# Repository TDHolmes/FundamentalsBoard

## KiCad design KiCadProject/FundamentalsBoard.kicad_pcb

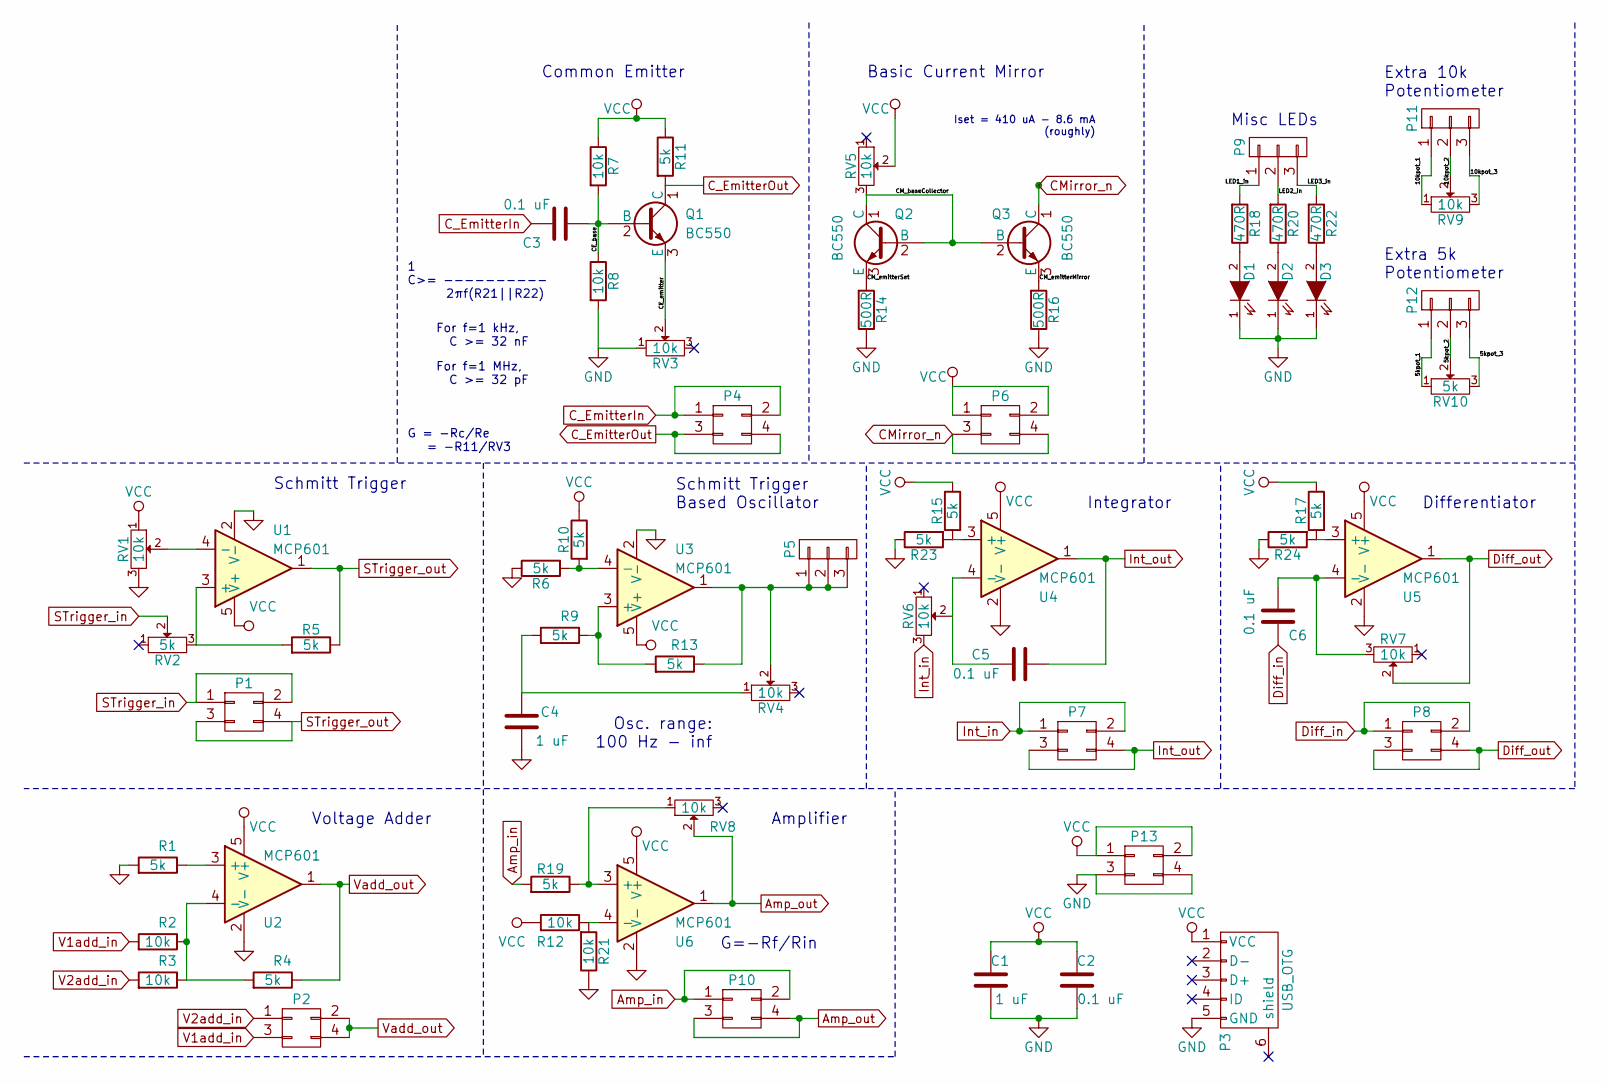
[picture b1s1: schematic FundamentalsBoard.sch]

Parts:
C1, C4: 1 uF; C_0603
C2, C3, C5, C6: 0.1 uF; C_0603
D1, D2, D3: LED; LED_0603
P1, P2, P4, P6, P7, P8, P10, P13: CONN_02X02; Pin_Header_Straight_2x02
P3: USB_OTG; 2013499-1
P5, P9, P11, P12: CONN_01X03; Pin_Header_Straight_1x03
Q1, Q2, Q3: BC550; SOT-23
R1, R4, R5, R6, R9, R10, R11, R13, R15, R17, R19, R23, R24: 5k; R_0603
R2, R3, R7, R8, R12, R21: 10k; R_0603
R14, R16: 500R; R_0603
R18, R20, R22: 470R; R_0603
RV1, RV3, RV4, RV5, RV6, RV7, RV8, RV9: 10k; ST-4
RV2, RV10: 5k; ST-4
U1, U2, U3, U4, U5, U6: MCP601; SOT-23-5

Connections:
/5kpot_1: P12.1, RV10.1
/5kpot_2: P12.2, RV10.2
/5kpot_3: P12.3, RV10.3
/10kpot_1: P11.1, RV9.1
/10kpot_2: P11.2, RV9.2
/10kpot_3: P11.3, RV9.3
/CE_base: C3.1, Q1.2 (B), R7.2, R8.1
/CE_emitter: Q1.3 (E), RV3.2
/CM_baseCollector: Q2.1 (C), Q2.2 (B), Q3.2 (B), RV5.3
/CM_emitterMirror: Q3.3 (E), R16.2
/CM_emitterSet: Q2.3 (E), R14.2
/LED1_in: P9.1, R18.2
/LED2_in: P9.2, R20.2
/LED3_in: P9.3, R22.2
Amp_in: P10.1, P10.2, R19.2
Amp_out: P10.3, P10.4, RV8.2, U6.1
CMirror_n: P6.3, P6.4, Q3.1 (C)
C_EmitterIn: C3.2, P4.1, P4.2
C_EmitterOut: P4.3, P4.4, Q1.1 (C), R11.2
Diff_in: C6.1, P8.1, P8.2
Diff_out: P8.3, P8.4, RV7.2, U5.1
GND: C1.1, C2.1, C4.1, D1.1 (K), D2.1 (K), D3.1 (K), P3.5 (GND), P13.3, P13.4, R1.2, R6.1, R8.2, R14.1, R16.1, R21.1, R23.1, R24.1, RV1.3, RV3.1, U1.2 (V-), U2.2 (V-), U3.2 (V-), U4.2 (V-), U5.2 (V-), U6.2 (V-)
Int_in: P7.1, P7.2, RV6.3
Int_out: C5.2, P7.3, P7.4, U4.1
unnamed: C4.2, R9.2, RV4.1
unnamed: C5.1, U4.4 (-)
unnamed: C6.2, RV7.3, U5.4 (-)
unnamed: D1.2 (A), R18.1
unnamed: D2.2 (A), R20.1
unnamed: D3.2 (A), R22.1
unnamed: P5.1, P5.2, P5.3, R13.1, RV4.2, U3.1
unnamed: R1.1, U2.3 (+)
unnamed: R2.1, R3.1, R4.2, U2.4 (-)
unnamed: R5.2, RV2.3, U1.3 (+)
unnamed: R6.2, R10.2, U3.4 (-)
unnamed: R12.1, R21.2, U6.4 (-)
unnamed: R9.1, R13.2, U3.3 (+)
unnamed: R15.2, R23.2, U4.3 (+)
unnamed: R17.2, R24.2, U5.3 (+)
unnamed: R19.1, RV8.1, U6.3 (+)
unnamed: RV1.2, U1.4 (-)
STrigger_in: P1.1, P1.2, RV2.2
STrigger_out: P1.3, P1.4, R5.1, U1.1
V1add_in: P2.3, R2.2
V2add_in: P2.1, R3.2
VCC: C1.2, C2.2, P3.1 (VCC), P6.1, P6.2, P13.1, P13.2, R7.1, R10.1, R11.1, R12.2, R15.1, R17.1, RV1.1, RV5.2, U1.5 (V+), U2.5 (V+), U3.5 (V+), U4.5 (V+), U5.5 (V+), U6.5 (V+)
Vadd_out: P2.2, P2.4, R4.1, U2.1

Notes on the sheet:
Common Emitter
Basic Current Mirror
1 C>= ---------- 2πf(R21||R22)
G = -Rc/Re = -R11/RV3
For f=1 kHz, C >= 32 nF
For f=1 MHz, C >= 32 pF
Extra 5k Potentiometer
Extra 10k Potentiometer
Schmitt Trigger
Schmitt Trigger Based Oscillator
Osc. range: 100 Hz - inf
Integrator
Differentiator
Amplifier
G=-Rf/Rin
Voltage Adder
Misc LEDs
Iset = 410 uA - 8.6 mA (roughly)

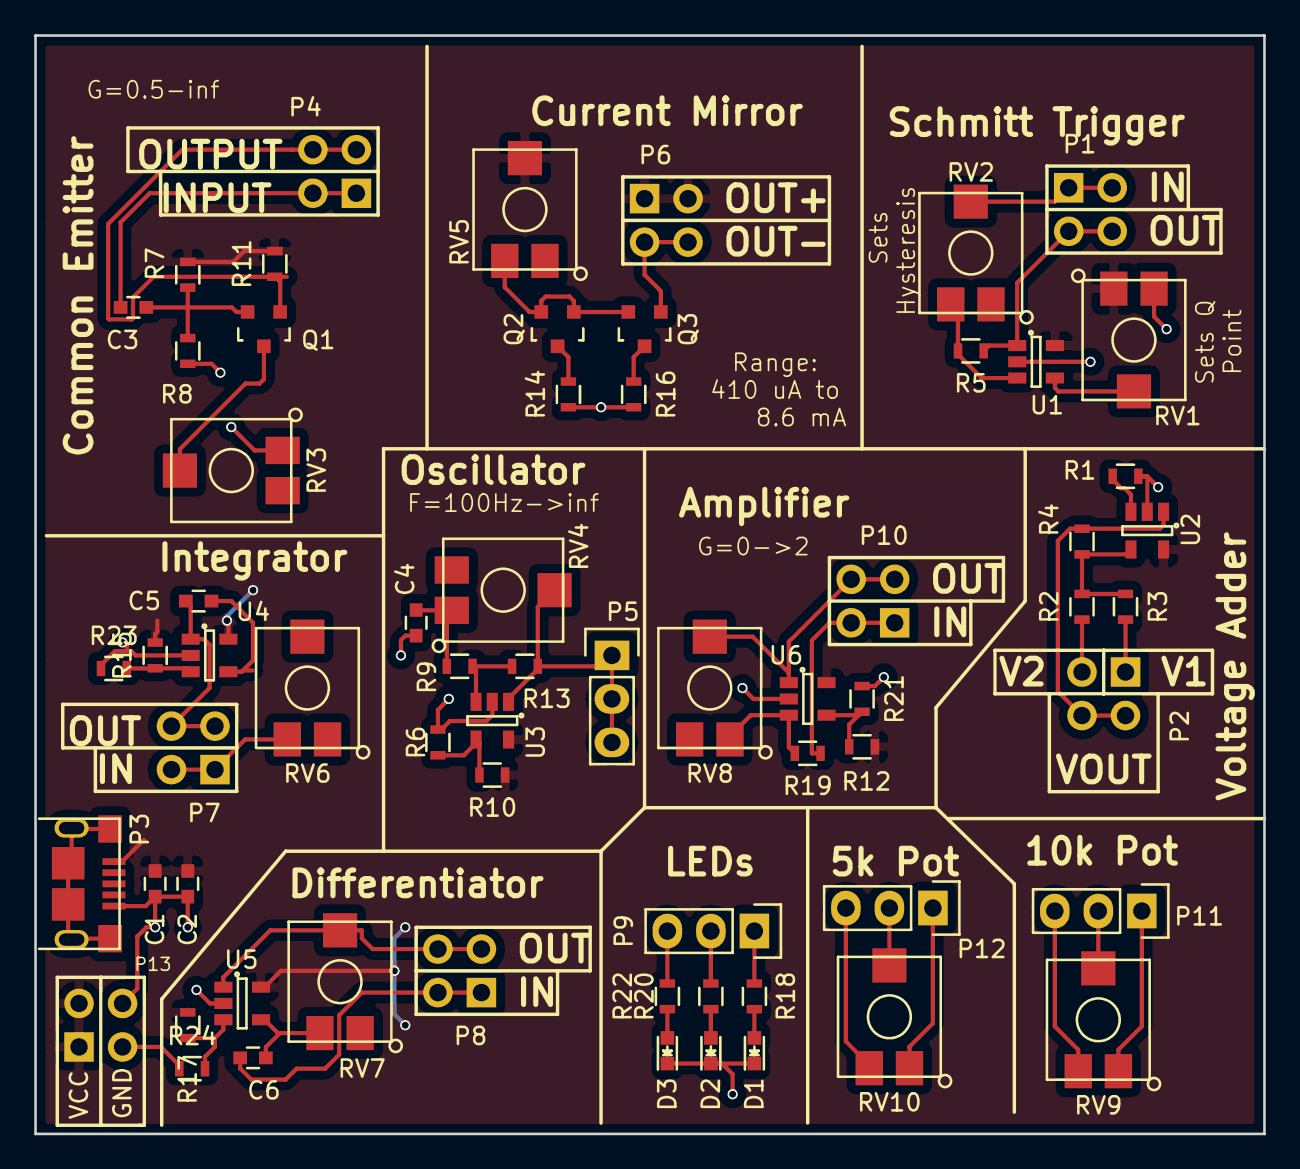
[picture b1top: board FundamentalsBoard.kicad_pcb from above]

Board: 2 copper layers, 71.8 x 64.1 mm, 65 parts (0 on the bottom side), 47 nets.

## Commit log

2016-12-04 Initial Commit
    Added all the files
2016-12-05 Adding a gitignore file
2016-12-06 Added Footprints
    Added footprint types to most components
2016-12-06 Initial export to the board.
2016-12-10 Initial layout
2016-12-10 Improved layout
2016-12-12 Final routing and Gerber export
2016-12-18 Corrected mistake in Amplifier feedback
2016-12-20 Fixed version number
